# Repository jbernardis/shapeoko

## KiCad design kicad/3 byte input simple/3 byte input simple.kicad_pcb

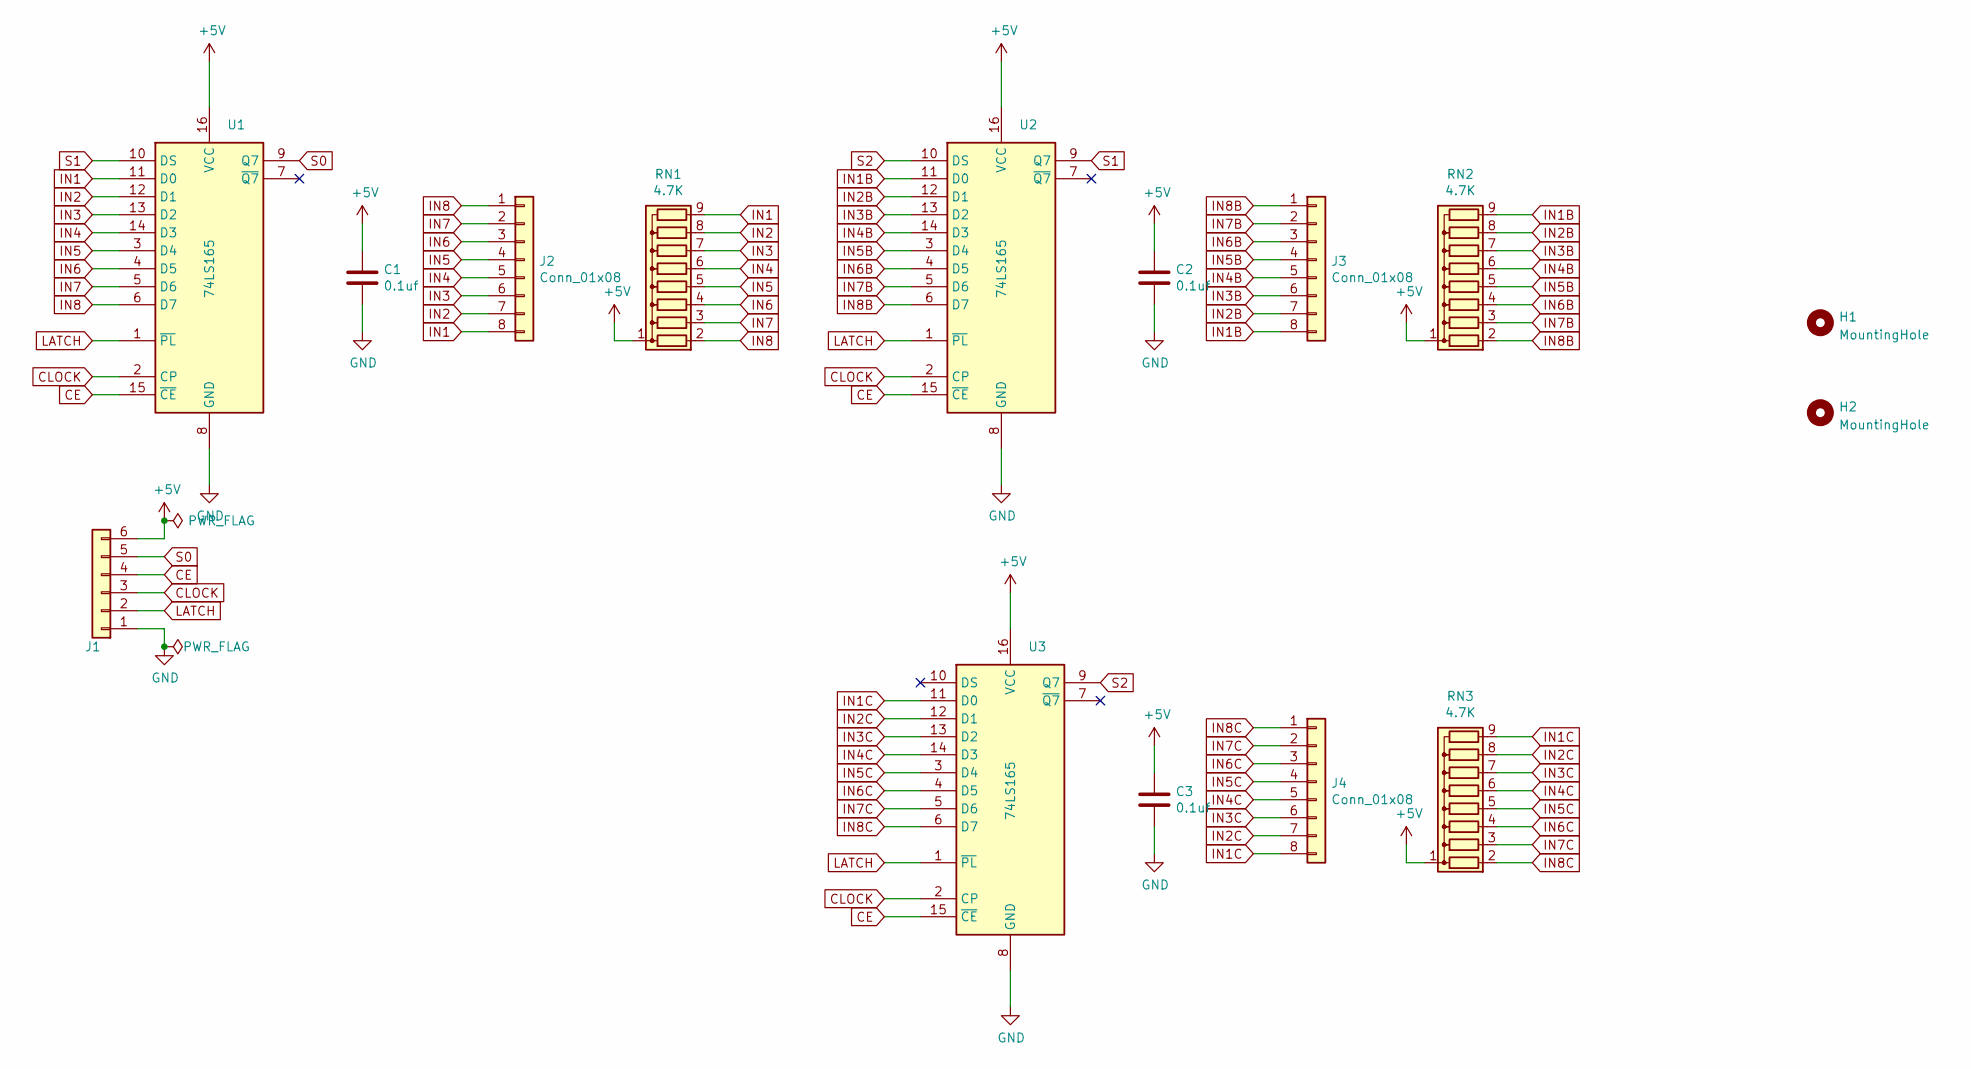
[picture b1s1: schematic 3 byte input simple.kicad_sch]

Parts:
C1, C2, C3: 0.1uf; C_Disc_D5.0mm_W2.5mm_P2.50mm
H1, H2: MountingHole; MountingHole_3.2mm_M3
J1: Conn_01x06; PinHeader_1x06_P2.54mm_Horizontal
J2, J3, J4: Conn_01x08; PinHeader_1x08_P2.54mm_Vertical
RN1, RN2, RN3: 4.7K; R_Array_SIP9
U1, U2, U3: 74LS165; DIP-16_W7.62mm

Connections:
+5V: C1.1, C2.1, C3.1, J1.6, RN1.1 (common), RN2.1 (common), RN3.1 (common), U1.16 (VCC), U2.16 (VCC), U3.16 (VCC)
CE: J1.4, U1.15 (~CE), U2.15 (~CE), U3.15 (~CE)
CLOCK: J1.3, U1.2 (CP), U2.2 (CP), U3.2 (CP)
GND: C1.2, C2.2, C3.2, J1.1, U1.8 (GND), U2.8 (GND), U3.8 (GND)
IN1: J2.8, RN1.9 (R8), U1.11 (D0)
IN1B: J3.8, RN2.9 (R8), U2.11 (D0)
IN1C: J4.8, RN3.9 (R8), U3.11 (D0)
IN2: J2.7, RN1.8 (R7), U1.12 (D1)
IN2B: J3.7, RN2.8 (R7), U2.12 (D1)
IN2C: J4.7, RN3.8 (R7), U3.12 (D1)
IN3: J2.6, RN1.7 (R6), U1.13 (D2)
IN3B: J3.6, RN2.7 (R6), U2.13 (D2)
IN3C: J4.6, RN3.7 (R6), U3.13 (D2)
IN4: J2.5, RN1.6 (R5), U1.14 (D3)
IN4B: J3.5, RN2.6 (R5), U2.14 (D3)
IN4C: J4.5, RN3.6 (R5), U3.14 (D3)
IN5: J2.4, RN1.5 (R4), U1.3 (D4)
IN5B: J3.4, RN2.5 (R4), U2.3 (D4)
IN5C: J4.4, RN3.5 (R4), U3.3 (D4)
IN6: J2.3, RN1.4 (R3), U1.4 (D5)
IN6B: J3.3, RN2.4 (R3), U2.4 (D5)
IN6C: J4.3, RN3.4 (R3), U3.4 (D5)
IN7: J2.2, RN1.3 (R2), U1.5 (D6)
IN7B: J3.2, RN2.3 (R2), U2.5 (D6)
IN7C: J4.2, RN3.3 (R2), U3.5 (D6)
IN8: J2.1, RN1.2 (R1), U1.6 (D7)
IN8B: J3.1, RN2.2 (R1), U2.6 (D7)
IN8C: J4.1, RN3.2 (R1), U3.6 (D7)
LATCH: J1.2, U1.1 (~PL), U2.1 (~PL), U3.1 (~PL)
S0: J1.5, U1.9 (Q7)
S1: U1.10 (DS), U2.9 (Q7)
S2: U2.10 (DS), U3.9 (Q7)

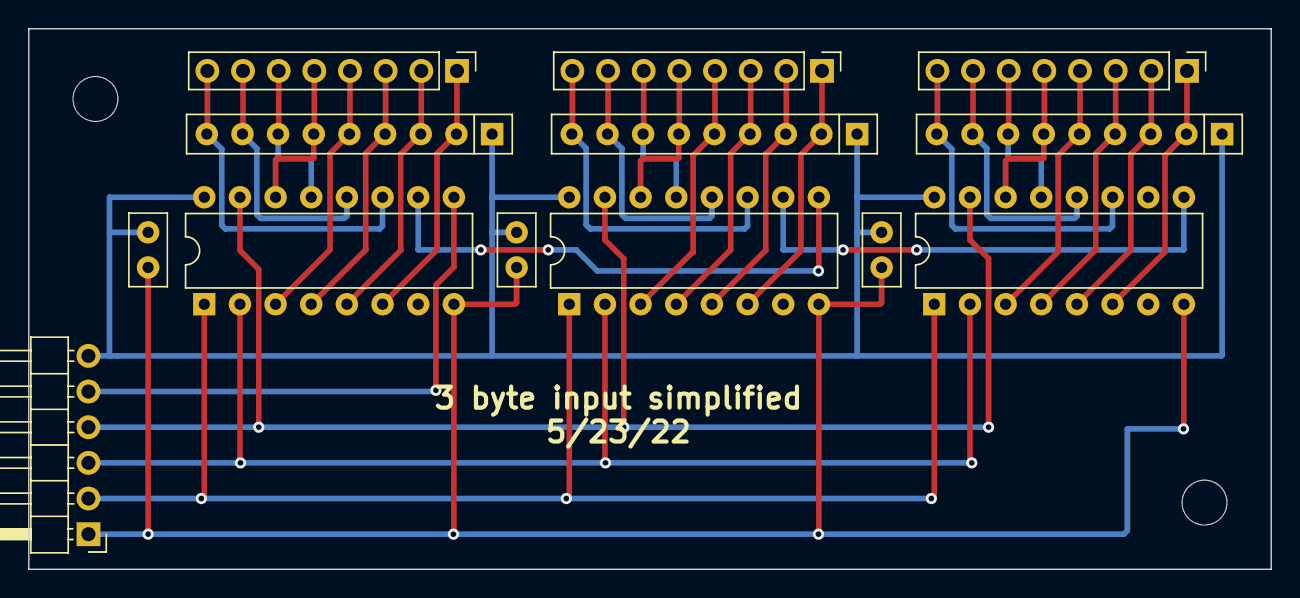
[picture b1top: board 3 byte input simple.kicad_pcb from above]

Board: 2 copper layers, 88.5 x 38.5 mm, 15 parts (0 on the bottom side), 32 nets.

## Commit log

2018-10-19 added all presets defined thus far
2018-12-15 resize/respace widgets for linux display, fix bug in rectangle
2018-12-15 Added an icon, changed out some deprecated menu calls
2019-04-08 changed 2d and 3d point properties to allow float values
2019-04-08 Fixed syntax issues detected by pycharm
2019-05-26 added some presets - fixes
2019-05-27 Adding 3 new presets
2022-05-13 removed obsolete code - added new code
2022-05-13 reorganized into raspberry pi and arduino
2022-05-13 added pendant sketch for arduino
2022-05-22 added beginnings of pendant code
2022-05-23 adding jogging logic
2022-05-24 updating pendant logic to use alternate circuit
2022-05-24 added begin call for buttons
2022-05-25 added schematic got buttonlayout and openscad file for correcponding bezel
2022-05-30 updates to pendant case design
2022-05-30 designed z3 back
2022-05-30 re-designed full back to include new z3 back
2022-06-05 starting display logic for rpi
2022-06-06 laying out main status screen
2022-06-07 first round of debugging with position display
2022-06-07 Continuing to implement GUI interface
2022-06-08 restructured code so main class is shapeoko instead of grbl
2022-06-12 continues development and debugging
2022-06-12 modifications for LCD dimensions
2022-06-12 added 3d designs for lcd clips
2022-06-13 added logic for check size, send gcode file
2022-06-14 still debugging
2022-06-14 Added hold feed.resume.soft reset, ability to see line number
2022-06-14 should have been part of last commit
2022-06-14 debugging session
2022-06-14 check in for next round of debug
2022-06-14 another round of debugging
2022-06-15 starting to work on status panel,
2022-06-15 continued debugging
    Please enter the commit message for your changes. Lines starting
2022-06-15 started implementation of jog panel
2022-06-15 debugging jog panel
2022-06-15 continue to fill out jog panel
2022-06-15 found a workaround for dialog box positioning
2022-06-15 greyed icons, check buttons to help diles dlg
2022-06-16 improved classification of inbound messages
2022-06-16 adding log and config panels
2022-06-17 debugging new stat and log panels
2022-06-17 implemented framework for log panel
2022-06-17 check in before trip
2022-06-21 config panel, file manager utility
2022-06-21 laying out log panel
2022-06-21 final(?) changes to log panel - only config panel remains
2022-06-21 updated todo file
2022-06-22 adding in logic got config lanel
2022-06-22 debugged the config panel
2022-06-24 implementing HTTP server framework only for now
2022-06-24 debugging of http interface
2022-06-24 added http command to retrieve config - testing
2022-06-24 got getcfg and setsfg working in http interface
2022-06-24 added http commands to exit and shutdown
2022-06-25 finalizing - get ready to deploy
2022-06-25 using sizers for window layout
2022-06-25 final sizing and widget positioning for linux
2022-06-25 added getpos http command to give printing pos
2022-06-25 changed some directory names, changed position http command to getjob
2022-06-25 debugged getjob http command
2022-06-26 implemented monitoring utility
2022-06-27 finishing up monitor - icons and tweaking GL canvas
2022-06-27 changed logic to allow operation without pendant
2022-06-30 added logic to drain queue if an alarm occurs
2022-06-30 renamed main file as controller.py
2022-06-30 added version string
2022-06-30 debugged adding grbl version string to the display
2022-07-02 added sketch for rpm
2022-07-03 removed os-specific code configuration files
2022-07-05 added tool following to monitor
2022-07-05 tweaking
2022-07-05 tweaks and fixes
2022-07-06 added generic command to http interface, dlg box for job completion
2022-07-06 working on pop-up when a job finishes
2022-07-07 testing
2022-07-07 updated front panel so there is room for text
2022-07-08 added gcode for front panel
2022-07-16 added home command and button to jog panel
2022-07-16 working out proper handling of home button
2022-07-16 still working on it
2022-07-16 restructured send q to not hang forever if no response
2022-07-17 more debugging
2022-07-17 still working on message timeing
2022-07-17 debugging
2022-07-17 starting implementation of spindle panel
2022-07-17 debugged up and down arrows on job panel
2022-07-18 filling out spindle panel
2022-07-18 got spindlepanel working for spindle speeds and on/off
2022-07-18 started implementation of probe
2022-07-18 added logic to reset Z height based on probing
2022-07-19 starting to add overrides
2022-07-19 finalized spindle panel - to be renamed overrides
2022-07-19 changed spindlepanel to override panel
2022-07-19 changed menu to be at bottom of screen
2022-07-20 widened bitmaps for menu, up/down on config
2022-07-20 copied reset butins to DRO, added diagonal jogging
2022-07-20 fixes to latest code
2022-07-20 changes to icons, removed DEPLOYED
2022-07-23 added exit panel permanently
2022-07-24 debugged exit panel
2022-07-24 added diagonal jogging to pendant
2022-08-03 adding logic to block certain actions if not in correct status
2022-08-03 finished jog panel check for valid state
2022-08-11 added file management commands t ohttp server
2024-11-11 long overdue checkin
2025-07-16 removed kicad files that were here incorrectly
